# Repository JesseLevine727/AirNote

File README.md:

# AirNote

A touchless musical instrument built around a fully integrated RP2040,
VL53L1X distance sensor and MAX98357A speaker amplifier. One hand selects
eleven pentatonic notes over two octaves. The design uses a four-layer PCB
and factory assembly, with an external 8 ohm speaker.

**Engineering prototype, rev 0.2. The first-article order package has passed
static review and is ready to order; nothing is ordered or physically validated yet.**
Use [the independent review status](reviews/REVIEW_STATUS.md) for current
failures, passes and pending evidence. A schematic check or firmware build
does not establish that the assembled instrument works.

## Open the design

Open [hardware/airnote.kicad_pro](hardware/airnote.kicad_pro) in KiCad 9.0.9
or newer. The project contains three schematic sheets and the PCB. Project
libraries accompany the files. The generated schematic can also be read in
[hardware/outputs/airnote-schematic.pdf](hardware/outputs/airnote-schematic.pdf).

[View the PCB render](hardware/outputs/airnote-board.png). Some parts, including
the volume pot, mute switch and amplifier, have no installed 3D body model;
the render shows their footprints. Use the BOM and assembly drawing for the
fitted-part list, and verify mechanical dimensions from their drawings.

The [BOM](hardware/bom.csv) identifies exact components with their LCSC part
numbers for JLCPCB assembly. The fabricator, stackup and USB geometry are
recorded in the [fabrication plan](docs/fabrication_plan.md); stock and
prices are a snapshot and must be re-checked on the day of ordering.
Manufacturing outputs remain engineering review artifacts until the
independent review of the current revision passes.

## Try the sound

[Listen to the synthesized scale](artifacts/synth-preview.wav). This WAV is
rendered by the same software oscillator used in firmware; it is **not a
recording of the PCB, amplifier or speaker**.

## Build and verify

Run from this directory. Native behavioral tests need CMake and a C++17
compiler; the device build additionally needs `arm-none-eabi-gcc`, Python 3
and Git. KiCad's Python module is used by the hardware tools.

```sh
cmake -S . -B build/host
cmake --build build/host -j 4
ctest --test-dir build/host --output-on-failure

python3 tools/fetch_dependencies.py
cmake -S firmware -B build/firmware
cmake --build build/firmware -j 8
```

The firmware build produces `build/firmware/airnote.uf2` and `airnote.elf`.
The captured build is also available as [artifacts/airnote.uf2](artifacts/airnote.uf2),
with source and binary checksums in `artifacts/firmware-evidence.json`.
The SDK may fetch/build its own `picotool` utility on the first build. Runtime
dependencies are pinned in `tools/fetch_dependencies.py`; the vendored sensor
and audio transport adaptations retain their licenses and provenance.

To regenerate the software sound preview:

```sh
build/host/render_demo artifacts/synth-preview.wav
```

Independent reviewer tests and artifact checks live in `reviews/`. The
reviewer owns those checks separately from the implementation. Their result
reports distinguish logic/net-mapping evidence from routing and physical tests.

## Documents

- [Requirements, targets and three-agent workflow](docs/requirements.md)
- [Bring-up, programming, equipment and calibration procedure](docs/bringup.md)
- [Power and thermal allocations](docs/power_budget.md)
- [Fabrication and sourcing plan (JLCPCB)](docs/fabrication_plan.md)
- [Draft factory assembly brief](docs/assembly_request.md)
- [Independent review checklist](reviews/CHECKLIST.md)
- [Current review status](reviews/REVIEW_STATUS.md)
- [Exact part list](hardware/bom.csv)
- [Firmware pin assignment](firmware/include/boards/airnote.h)

Normal PLAY operation uses a specified 5 V adapter; programming/USB diagnostics
use the hardware MUTE position. Firmware also latches a USB host mute, starts
peripherals only after configuration or a deliberate adapter PLAY sequence,
and parks audio after USB suspend/deconfiguration until power-cycle. These
policies do not replace current/inrush/suspend measurements. The initial
distance correction is zero and has not been calibrated to a physical board.

The overseer coordinates the specification and integration, the implementer
creates the hardware, and the reviewer independently checks the artifacts and
tests. Neither factory assembly nor clean ERC/DRC counts as physical validation.

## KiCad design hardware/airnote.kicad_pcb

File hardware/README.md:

# AirNote hardware — engineering prototype

Open **airnote.kicad_pro** in KiCad 9. The three editable schematic sheets and routed four-layer PCB are the canonical design. The current native checks report **0 ERC violations; 0 DRC violations, 0 unconnected items and 0 schematic/PCB parity issues**. These are software checks; a physical board has not been built or tested.

- [Schematic PDF](outputs/airnote-schematic.pdf)
- [Board render](outputs/airnote-board.png)
- [Assembly drawing, including component references](outputs/airnote-assembly.pdf)
- [Four copper layers](outputs/airnote-copper.pdf)
- [Exact component BOM](bom.csv)
- [Draft fabrication and assembly exports](outputs/DRAFT-fabrication/)
- [Native ERC](reports/erc-final.json) and [DRC](reports/drc-final.json)
- [Independent review](../reviews/REVIEW_STATUS.md)

The render is illustrative: some exact component 3D models are absent, while their electrical footprints and assembly references remain present.

The board is 90 × 70 mm with four M2.5 mounting holes and three global fiducials (FID1 53.5/61.5, FID2 61.5/116.5, FID3 130.0/53.5 mm; 1 mm copper, 2 mm mask opening, board-only, excluded from BOM and position files). Signals route on F.Cu and B.Cu; In1.Cu and In2.Cu are ground reference planes. There are also outer ground pours. Minimum designed track/clearance is 0.15/0.127 mm; through vias are 0.45 mm copper with 0.20 mm drill. These are copper-path estimates from `reviews/inspect_trace_paths.py`, not measured supply integrity: IOVDD pin 22 to C6 about 2.9 mm (C6 GND pad via about 0.4 mm from the pad), DVDD pin 23 to C11 about 1.1 mm, IOVDD pin 33 to C7 about 1.6 mm and flash VCC to C15 about 3.1 mm. Crystal startup and oscillator margin remain bench checks.

The +5V rail after F1 is 0.4 mm wide (rev 0.2 review follow-up). F1 → U3 input and C16 is now 36.6 mm of 0.4 mm F.Cu with no vias, about 0.05 Ω estimated; it was 0.15 mm and about 0.12 Ω. F1 → U5 VDD/PVDD is 0.4 mm on F.Cu and on the B.Cu run, about 0.12 Ω estimated; it was 0.15 mm and about 0.31 Ω. At U5 the B.Cu-to-F.Cu change now has two vias in parallel. The C21/C22 bulk link is 0.4 mm. Three short sections stay narrower:

- The U5 pin 7/8 stubs are 0.3 mm, the pad width.
- The U3 EN tie (pin 3 to pin 1) is 0.15 mm; it carries no load current.
- The single F.Cu-to-B.Cu via beside SW2 and C19 has no room for a second via without rerouting RUN and SENSOR_XSHUT.

Resistances are copper estimates, not measurements.

The MCU is RP2040 with W25Q16JVSNIQ flash and a 12 MHz crystal. VL53L1CXV0FY/1 uses 3.3 V AVDD, 3.3 V I2C pull-ups and explicit 2V8-mode initialization. MAX98357AETE+T drives an external 8 Ω speaker; neither speaker terminal may connect to ground. Its GAIN pin floats for 9 dB, and SD high selects LEFT; firmware sends the same sample in both channels. A 10 kΩ resistor between GP14 and AMP_SD limits contention when the hardware MUTE switch forces shutdown. A separate switch pole makes GP15 low in MUTE. The volume potentiometer has a 1 MΩ ADC pull-down so an open wiper tends toward silence.

| Function | RP2040 GPIO |
|---|---:|
| I2C SDA / SCL | 0 / 1 |
| VL53L1X XSHUT / interrupt | 2 / 3 |
| I2S data / bit clock / LR clock | 10 / 11 / 12 |
| Amplifier enable / active-low mute sense | 14 / 15 |
| Status LED / volume ADC | 25 / 26 |

Use a regulated USB 5 V supply rated at least 1 A for PLAY. Set MUTE before connecting a computer for programming. The 250 mA USB descriptor is a declaration, not a measurement. USB inrush, configured current, suspend current, regulator temperature and actual speaker power remain physical test gates. See [calculated power budget](../docs/power_budget.md) and [bring-up procedure](../docs/bringup.md).

Factory assembly is required for the optical LGA and MCU/amp exposed-pad packages. Before release, the assembler must confirm the exact MPN supply, four-layer stackup, optical-device dry/no-wash process, MSL handling, sensor liner removal, post-reflow offset calibration, paste stencil and exposed-pad via fill/cap or equivalent validated process. The board includes thermal vias in the MCU and amplifier exposed pads. The external speaker, mating cable and power adapter are not PCBA BOM items. Through-hole controls/connectors require an assembly quote as well. Verify actual switch lever direction against MUTE/PLAY silkscreen during bring-up. No parts or boards have been ordered and no quoted total cost is available.

## Layout and sourcing notes

### Stackup

The board stackup is JLCPCB JLC04161H-7628, the chosen stackup per `docs/fabrication_plan.md` (1.6 mm nominal; KiCad sum 1.606 mm including 0.01 mm masks): F.Cu 0.035 / 7628 prepreg 0.2104 mm, εr 4.4 / In1.Cu 0.0152 / core 1.065 mm, εr 4.6 / In2.Cu 0.0152 / 7628 prepreg 0.2104 mm, εr 4.4 / B.Cu 0.035, solder mask both sides (εr 3.8). Re-check the stackup code on the order form. The copper finish is deliberately left unset in CAD (`None` in the Gerber job) because it is chosen on the order form: ENIG recommended, lead-free HASL acceptable. That is the user's decision.

### USB geometry

USB_DP, USB_DM, USB_DP_ESD, USB_DM_ESD, USB_DP_MCU and USB_DM_MCU are net class `USB_DIFF`: 0.25 mm traces, 0.15 mm pair gap (about 90 Ω differential on this stackup by the overseer's 2D field-solver estimate; USB full speed tolerates 90 Ω ±15%), 0.2 mm clearance to other nets, and a custom rule that keeps the outer GND pour 0.5 mm away so the pair is edge-coupled microstrip rather than coplanar. Neck-down to 0.15 mm happens at the J1, D1 and U1 pads, including two runs of about 3 mm through D1's pad gap. About 85% of each polarity runs at exactly 0.40 mm pitch. The uncoupled remainder is the J1 fan-out and duplicate-contact joins, the D1 pad entries and the staggered R8/R9. The whole path is on F.Cu with **zero vias**, over continuous In1.Cu GND (a script samples the trace footprint plus 0.1 mm and finds no In1 void or antipad under it).

- J1: the duplicated contacts are joined by short 0.15 mm stubs: DP (A6–B6) behind the pad row under the receptacle body, DM (A7–B7) in front of it. The pair leaves from B6/A7.
- D1 (USBLC6-2SC6) is about 15 mm along the pair from J1. The schematic order J1 → D1 → R8/R9 → U1 needs the pair to swap sides twice; both swaps happen inside D1 without vias. USB_DM runs through the gap between D1's pad columns to pin 3, and USB_DP_ESD leaves pin 6 through the same gap, using D1's internal pin 1–6 and 3–4 links as the crossovers. VBUS_RAW (pin 5) and GND (pin 2, own via) leave from the outer pad ends.
- R8/R9 sit side by side about 3 mm above U1 pins 47/46. The R → U1 section is matched within 0.23 mm (3.30 / 3.53 mm).
- Lengths, pad edge to pad edge, along the B6 and A7 trunks (reviewer's measurement, `reviews/layout-review.json`): J1 → D1 13.80 mm DP / 15.61 mm DM; D1 → R8/R9 43.66 / 41.40 mm; R8/R9 → U1 3.30 / 3.53 mm.
  - The per-section difference of about ±2 mm in the first two sections comes from where the D1 crossover puts the gap run (before the package for DM, after it for DP).
  - Through D1, the J1 → U1 totals are 60.76 mm DP and 60.53 mm DM, a 0.23 mm skew.
  - The USB-C duplicate-contact joins add orientation-dependent skew: up to about 2.8 mm with the plug on A6/A7 and 0.8 mm on B6/B7. That is about 17 ps, negligible against the 83 ns full-speed bit time.
- The pair is about 60 mm long (previously about 50 mm, routed as separate nets). It goes around the east side of the flash and approaches U1 from the north.
- USB impedance and differential behaviour are **not measured**. These are layout checks only. Request impedance control or an impedance coupon from the fabricator if the actual differential impedance matters.

### Crystal and RP2040 supply pins

Y1 (rotated −90°) sits directly below U1 pins 20/21. XIN is about 4.0–4.1 mm from pin 20 to Y1 pin 1 on F.Cu with no vias. XOUT runs about 0.8 mm straight into R1 (1 kΩ). XTAL_OUT runs about 4.1 mm from R1 pin 2, down the gap between Y1's pad columns, to Y1 pin 3. C1 and C2 are about 1 mm from Y1 pins 1 and 3 and have their own GND vias. Y1 GND pads 2 and 4 each have a GND via. U1 pin 19 GND, C5 and the F.Cu GND pour surround the network. No unrelated signal runs on F.Cu between the crystal network and U1 or under the crystal. The JLC listing for this crystal gives CL = 10 pF. C1/C2 stay at 15 pF: with about 3 pF stray that is about 10.5 pF, the RP2040 hardware design guide values. Frequency offset and startup margin must be measured at bring-up.

### Sourcing

`bom.csv` and every fitted schematic symbol carry an `LCSC` part number, and fitted footprints carry hidden `MPN`/`LCSC` fields for BOM/CPL generation. Passives use JLC Basic parts. R8/R9 (27 Ω, C25190) are JLC Extended. **Correction:** U2 is now W25Q16JVSNIQ, the 150-mil SOIC-8 that matches the placed SOIC-8_3.9x4.9 footprint. The previous W25Q16JVSSIQ is the 208-mil package, a part/footprint mismatch. Other substitutions:

- J1 is USB4105-GF-A-120 (same land pattern, 1.20 mm shell stakes).
- J2 is a generic straight 1x5 2.54 mm header (C32713271).
- RV1 is PTV09A-4015F-B103 (bushingless, 15 mm flat shaft). Bourns gives one recommended layout for all rear-mount PTV09 configurations, so the existing footprint is unchanged. The knob sits about 5 mm lower than with -1020F.

### Rev 0.2 review fixes

- The J1 shell stitching via at (67.80, 56.12) is removed (MFG-05). Its drill was 0.13 mm from the S1 shell slot, and the S1 pads are solid in GND on every layer.
- The reviewer's drill-web check (`reviews/inspect_layout.py`) now passes: via to via ≥ 0.2 mm, via to pad hole ≥ 0.45 mm.
- The C15 GND-pad via moved to (95.34, 66.94); its drill edge is 0.15 mm outside the pad.
- The board is marked rev 0.2: silkscreen "v0.2 ENGINEERING PROTOTYPE", PCB title block AirNote / 0.2 / 2026-10-10 (the Gerber job revision reads 0.2), and schematic title blocks rev 0.2.
- B.Silkscreen carries `JLCJLCJLCJLC` at (70, 90) so JLC prints its order number there.
- The JLC order files are generated by `tools/export_outputs.py`. See [the export README](outputs/DRAFT-fabrication/README.md) for upload steps.

## Re-export and regeneration

With KiCad 9 CLI installed, run from the repository root:

```sh
/usr/bin/python3 hardware/tools/export_outputs.py
```

This runs ERC and DRC, refuses failed checks, and regenerates PDF, render, Gerbers, drills, fitted BOM/positions, the JLC order files and an SHA-256 artifact manifest. It does not edit the canonical schematic or PCB. Position coordinates use KiCad's absolute origin in millimeters, with exported Y convention; the assembler must confirm rotations/origin. Test pads, mounting holes and fiducials are excluded from the position files. The export also writes the JLCPCB order package: `airnote-jlc-bom.csv`, `airnote-jlc-cpl.csv` (KiCad rotations, uncorrected) and `airnote-jlc-gerbers.zip`, all hashed in the artifact manifest.

`generate_hardware.py` creates only an initial schematic/placement in a **fresh separate directory**:

```sh
/usr/bin/python3 hardware/tools/generate_hardware.py --output-dir /tmp/airnote-rebuild
```

It intentionally refuses the canonical `hardware/` directory or an existing PCB output. The generator does **not** reproduce the final routed board: subsequent placement and local routing corrections live in the canonical editable PCB. Its output is a design-development starting point, not a replacement manufacturing source. Other scripts in `tools/` record the development routing stages and can overwrite a working PCB; do not rerun those on the canonical design. Historical router sessions and intermediate `reports/*.kicad_pcb` boards are development evidence, not order candidates. Use only `*-final.json` reports and the current artifact hashes for the final checkpoint. The custom rules in `airnote.kicad_dru` now carry explicit units; the earlier unit-less file was rejected by KiCad, so those rules had not been applied before.

Project-local libraries include a datasheet-correct MAX98357A exposed-pad symbol and exact ADI 90-0031 land pattern. J1's local footprint differs from the installed KiCad footprint only in two unplated peg-hole layer masks: `F&B.Cu` becomes `*.Cu`, matching KiCad's four-layer normalization. Pad locations, dimensions, drills, shell slots and contact mapping are unchanged. Standard native library footprints are embedded in the PCB and additional snapshots are retained locally.

References: [RP2040 hardware design guide](https://datasheets.raspberrypi.com/rp2040/hardware-design-with-rp2040.pdf), [official reference source](https://datasheets.raspberrypi.com/rp2040/Minimal-KiCAD.zip), [ST VL53L1X datasheet](https://www.st.com/resource/en/datasheet/vl53l1x.pdf), [MAX98357A datasheet](https://www.analog.com/media/en/technical-documentation/data-sheets/MAX98357A-MAX98357B.pdf), [ADI land pattern 90-0031](https://mds.analog.com/api/public/content/90-0031.pdf), [Bourns potentiometer drawing](https://www.bourns.com/docs/product-datasheets/ptv09.pdf). The downloaded Raspberry Pi source retains its original license in `reference/`; KiCad library snapshots originate from the installed KiCad libraries and retain their upstream licensing.

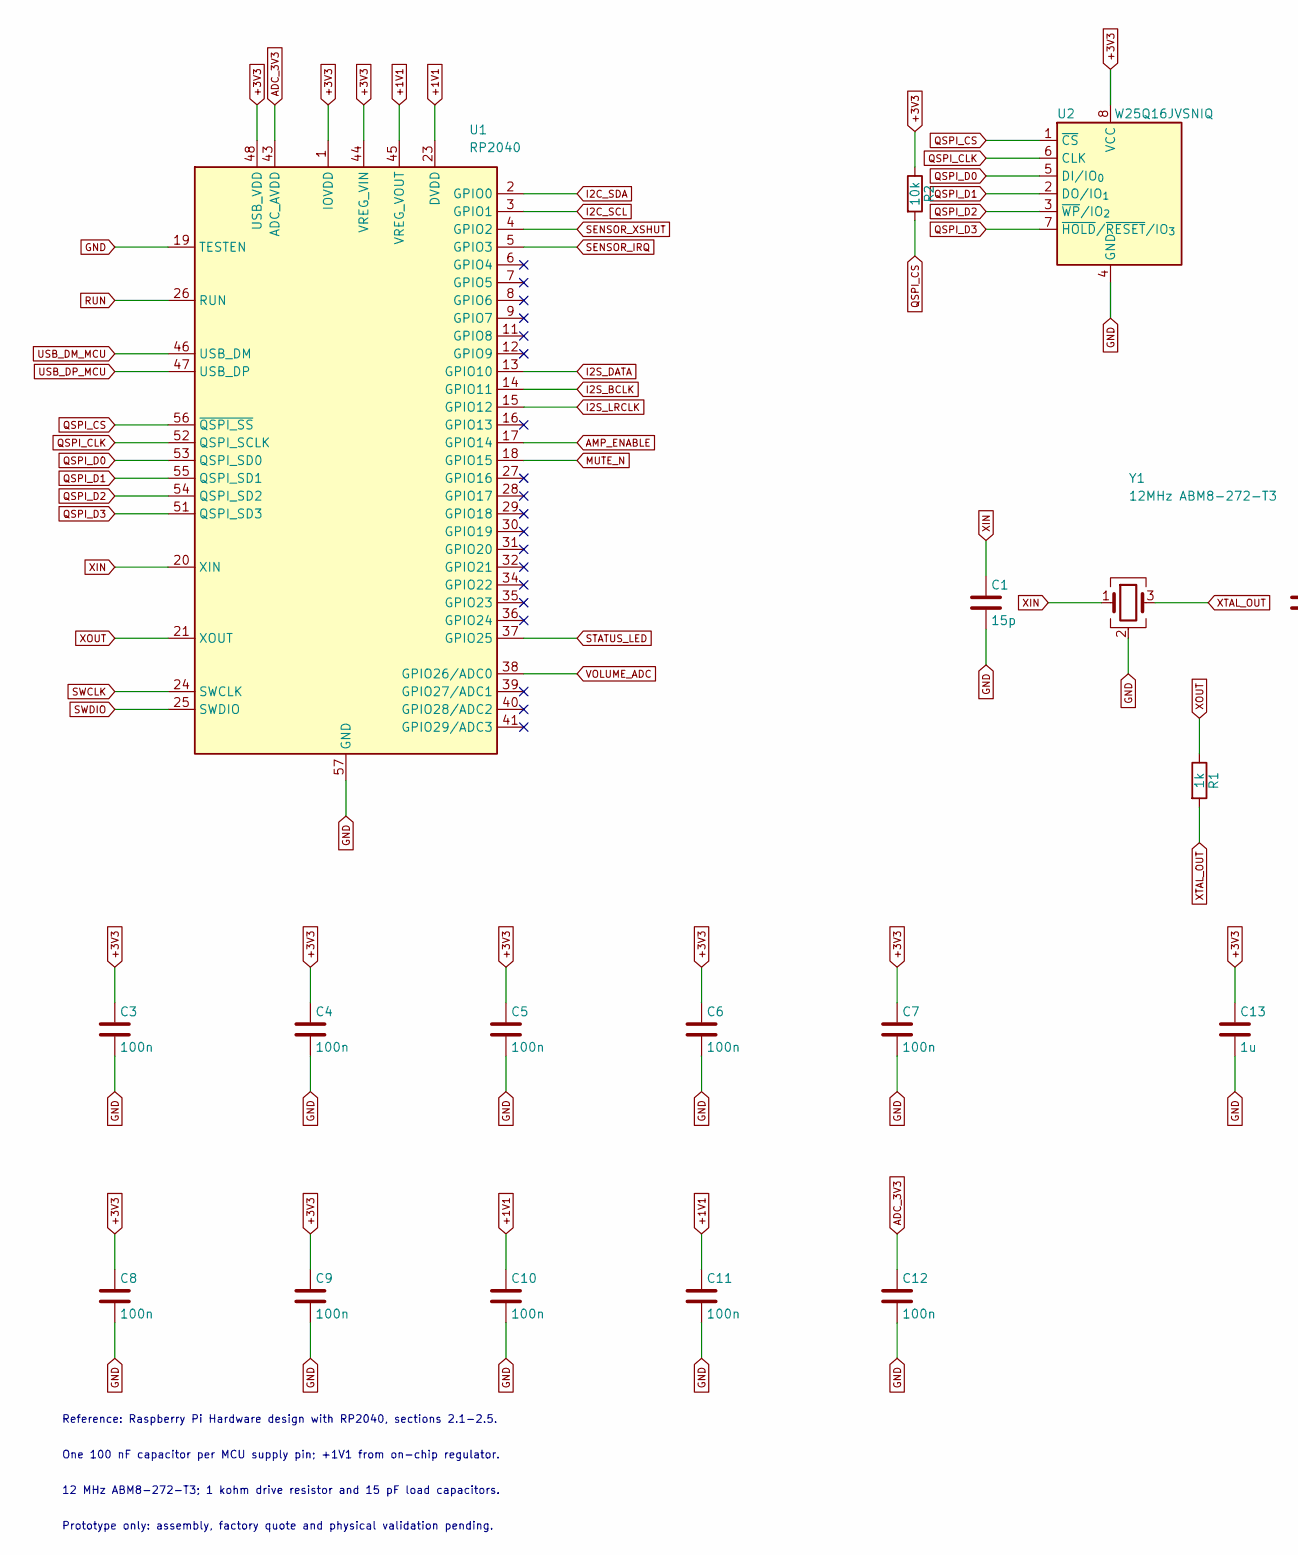
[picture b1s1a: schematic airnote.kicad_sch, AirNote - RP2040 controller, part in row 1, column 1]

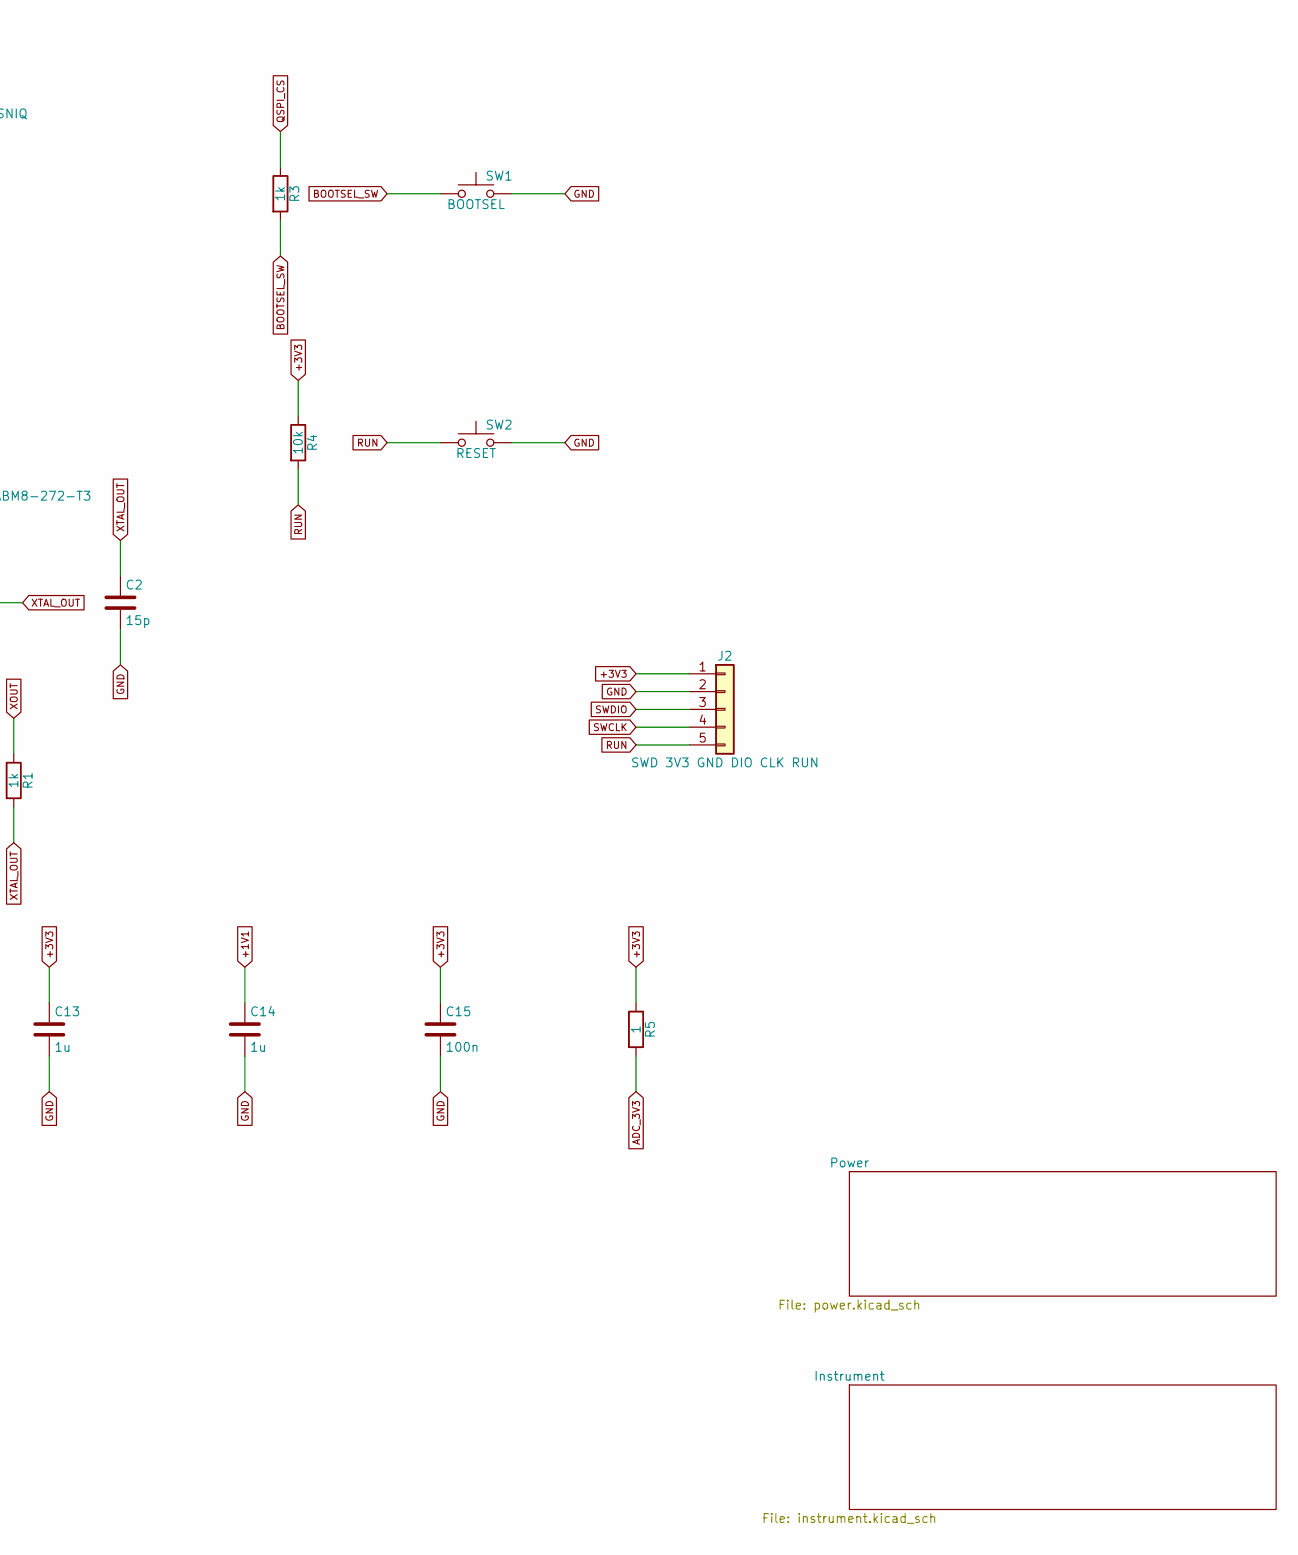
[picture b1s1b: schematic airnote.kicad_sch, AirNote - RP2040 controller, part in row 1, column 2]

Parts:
C1, C2: 15p; C_0603_1608Metric; MPN CL10C150JB8NNNC; LCSC C1644
C3, C4, C5, C6, C7, C8, C9, C10, C11, C12, C15: 100n; C_0603_1608Metric; MPN CC0603KRX7R9BB104; LCSC C14663
C13, C14: 1u; C_0603_1608Metric; MPN CL10A105KB8NNNC; LCSC C15849
J2: SWD 3V3 GND DIO CLK RUN; PinHeader_1x05_P2.54mm_Vertical; MPN HX PZ2.54-1x5P ZZ; LCSC C32713271
R1, R3: 1k; R_0603_1608Metric; MPN 0603WAF1001T5E; LCSC C21190
R2, R4: 10k; R_0603_1608Metric; MPN 0603WAF1002T5E; LCSC C25804
R5: 1; R_0603_1608Metric; MPN 0603WAF100KT5E; LCSC C22936
SW1: BOOTSEL; SW_SPST_TL3342; MPN TL3342F160QG; LCSC C2886898
SW2: RESET; SW_SPST_TL3342; MPN TL3342F160QG; LCSC C2886898
U1: RP2040; QFN-56-1EP_7x7mm_P0.4mm_EP3.2x3.2mm; MPN RP2040; LCSC C2040
U2: W25Q16JVSNIQ; SOIC-8_3.9x4.9mm_P1.27mm; MPN W25Q16JVSNIQ; LCSC C2456211
Y1: 12MHz ABM8-272-T3; Crystal_SMD_3225-4Pin_3.2x2.5mm; MPN ABM8-272-T3; LCSC C20625731

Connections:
+1V1: C10.1, C11.1, C14.1, U1.23 (DVDD), U1.45 (VREG_VOUT), U1.50 (DVDD); also elsewhere on the board
+3V3: C3.1, C4.1, C5.1, C6.1, C7.1, C8.1, C9.1, C13.1, C15.1, J2.1, R2.1, R4.1, R5.1, U1.1 (IOVDD), U1.10 (IOVDD), U1.22 (IOVDD), U1.33 (IOVDD), U1.42 (IOVDD), U1.44 (VREG_VIN), U1.48 (USB_VDD), U1.49 (IOVDD), U2.8 (VCC); also elsewhere on the board
ADC_3V3: C12.1, R5.2, U1.43 (ADC_AVDD)
AMP_ENABLE: U1.17 (GPIO14); also elsewhere on the board
BOOTSEL_SW: R3.2, SW1.1
GND: C1.2, C2.2, C3.2, C4.2, C5.2, C6.2, C7.2, C8.2, C9.2, C10.2, C11.2, C12.2, C13.2, C14.2, C15.2, J2.2, SW1.2, SW2.2, U1.19 (TESTEN), U1.57 (GND), U2.4 (GND), Y1.2 (G), Y1.4 (G); also elsewhere on the board
I2C_SCL: U1.3 (GPIO1); also elsewhere on the board
I2C_SDA: U1.2 (GPIO0); also elsewhere on the board
I2S_BCLK: U1.14 (GPIO11); also elsewhere on the board
I2S_DATA: U1.13 (GPIO10); also elsewhere on the board
I2S_LRCLK: U1.15 (GPIO12); also elsewhere on the board
MUTE_N: U1.18 (GPIO15); also elsewhere on the board
QSPI_CLK: U1.52 (QSPI_SCLK), U2.6 (CLK)
QSPI_CS: R2.2, R3.1, U1.56 (~QSPI_SS), U2.1 (~CS)
QSPI_D0: U1.53 (QSPI_SD0), U2.5 (DI/IO_{0})
QSPI_D1: U1.55 (QSPI_SD1), U2.2 (DO/IO_{1})
QSPI_D2: U1.54 (QSPI_SD2), U2.3 (~WP/IO_{2})
QSPI_D3: U1.51 (QSPI_SD3), U2.7 (~HOLD/~RESET/IO_{3})
RUN: J2.5, R4.2, SW2.1, U1.26 (RUN)
SENSOR_IRQ: U1.5 (GPIO3); also elsewhere on the board
SENSOR_XSHUT: U1.4 (GPIO2); also elsewhere on the board
STATUS_LED: U1.37 (GPIO25); also elsewhere on the board
SWCLK: J2.4, U1.24 (SWCLK)
SWDIO: J2.3, U1.25 (SWDIO)
USB_DM_MCU: U1.46 (USB_DM); also elsewhere on the board
USB_DP_MCU: U1.47 (USB_DP); also elsewhere on the board
VOLUME_ADC: U1.38 (GPIO26/ADC0); also elsewhere on the board
XIN: C1.1, U1.20 (XIN), Y1.1
XOUT: R1.1, U1.21 (XOUT)
XTAL_OUT: C2.1, R1.2, Y1.3

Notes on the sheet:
Reference: Raspberry Pi Hardware design with RP2040, sections 2.1-2.5.
One 100 nF capacitor per MCU supply pin; +1V1 from on-chip regulator.
12 MHz ABM8-272-T3; 1 kohm drive resistor and 15 pF load capacitors.
Prototype only: assembly, factory quote and physical validation pending.

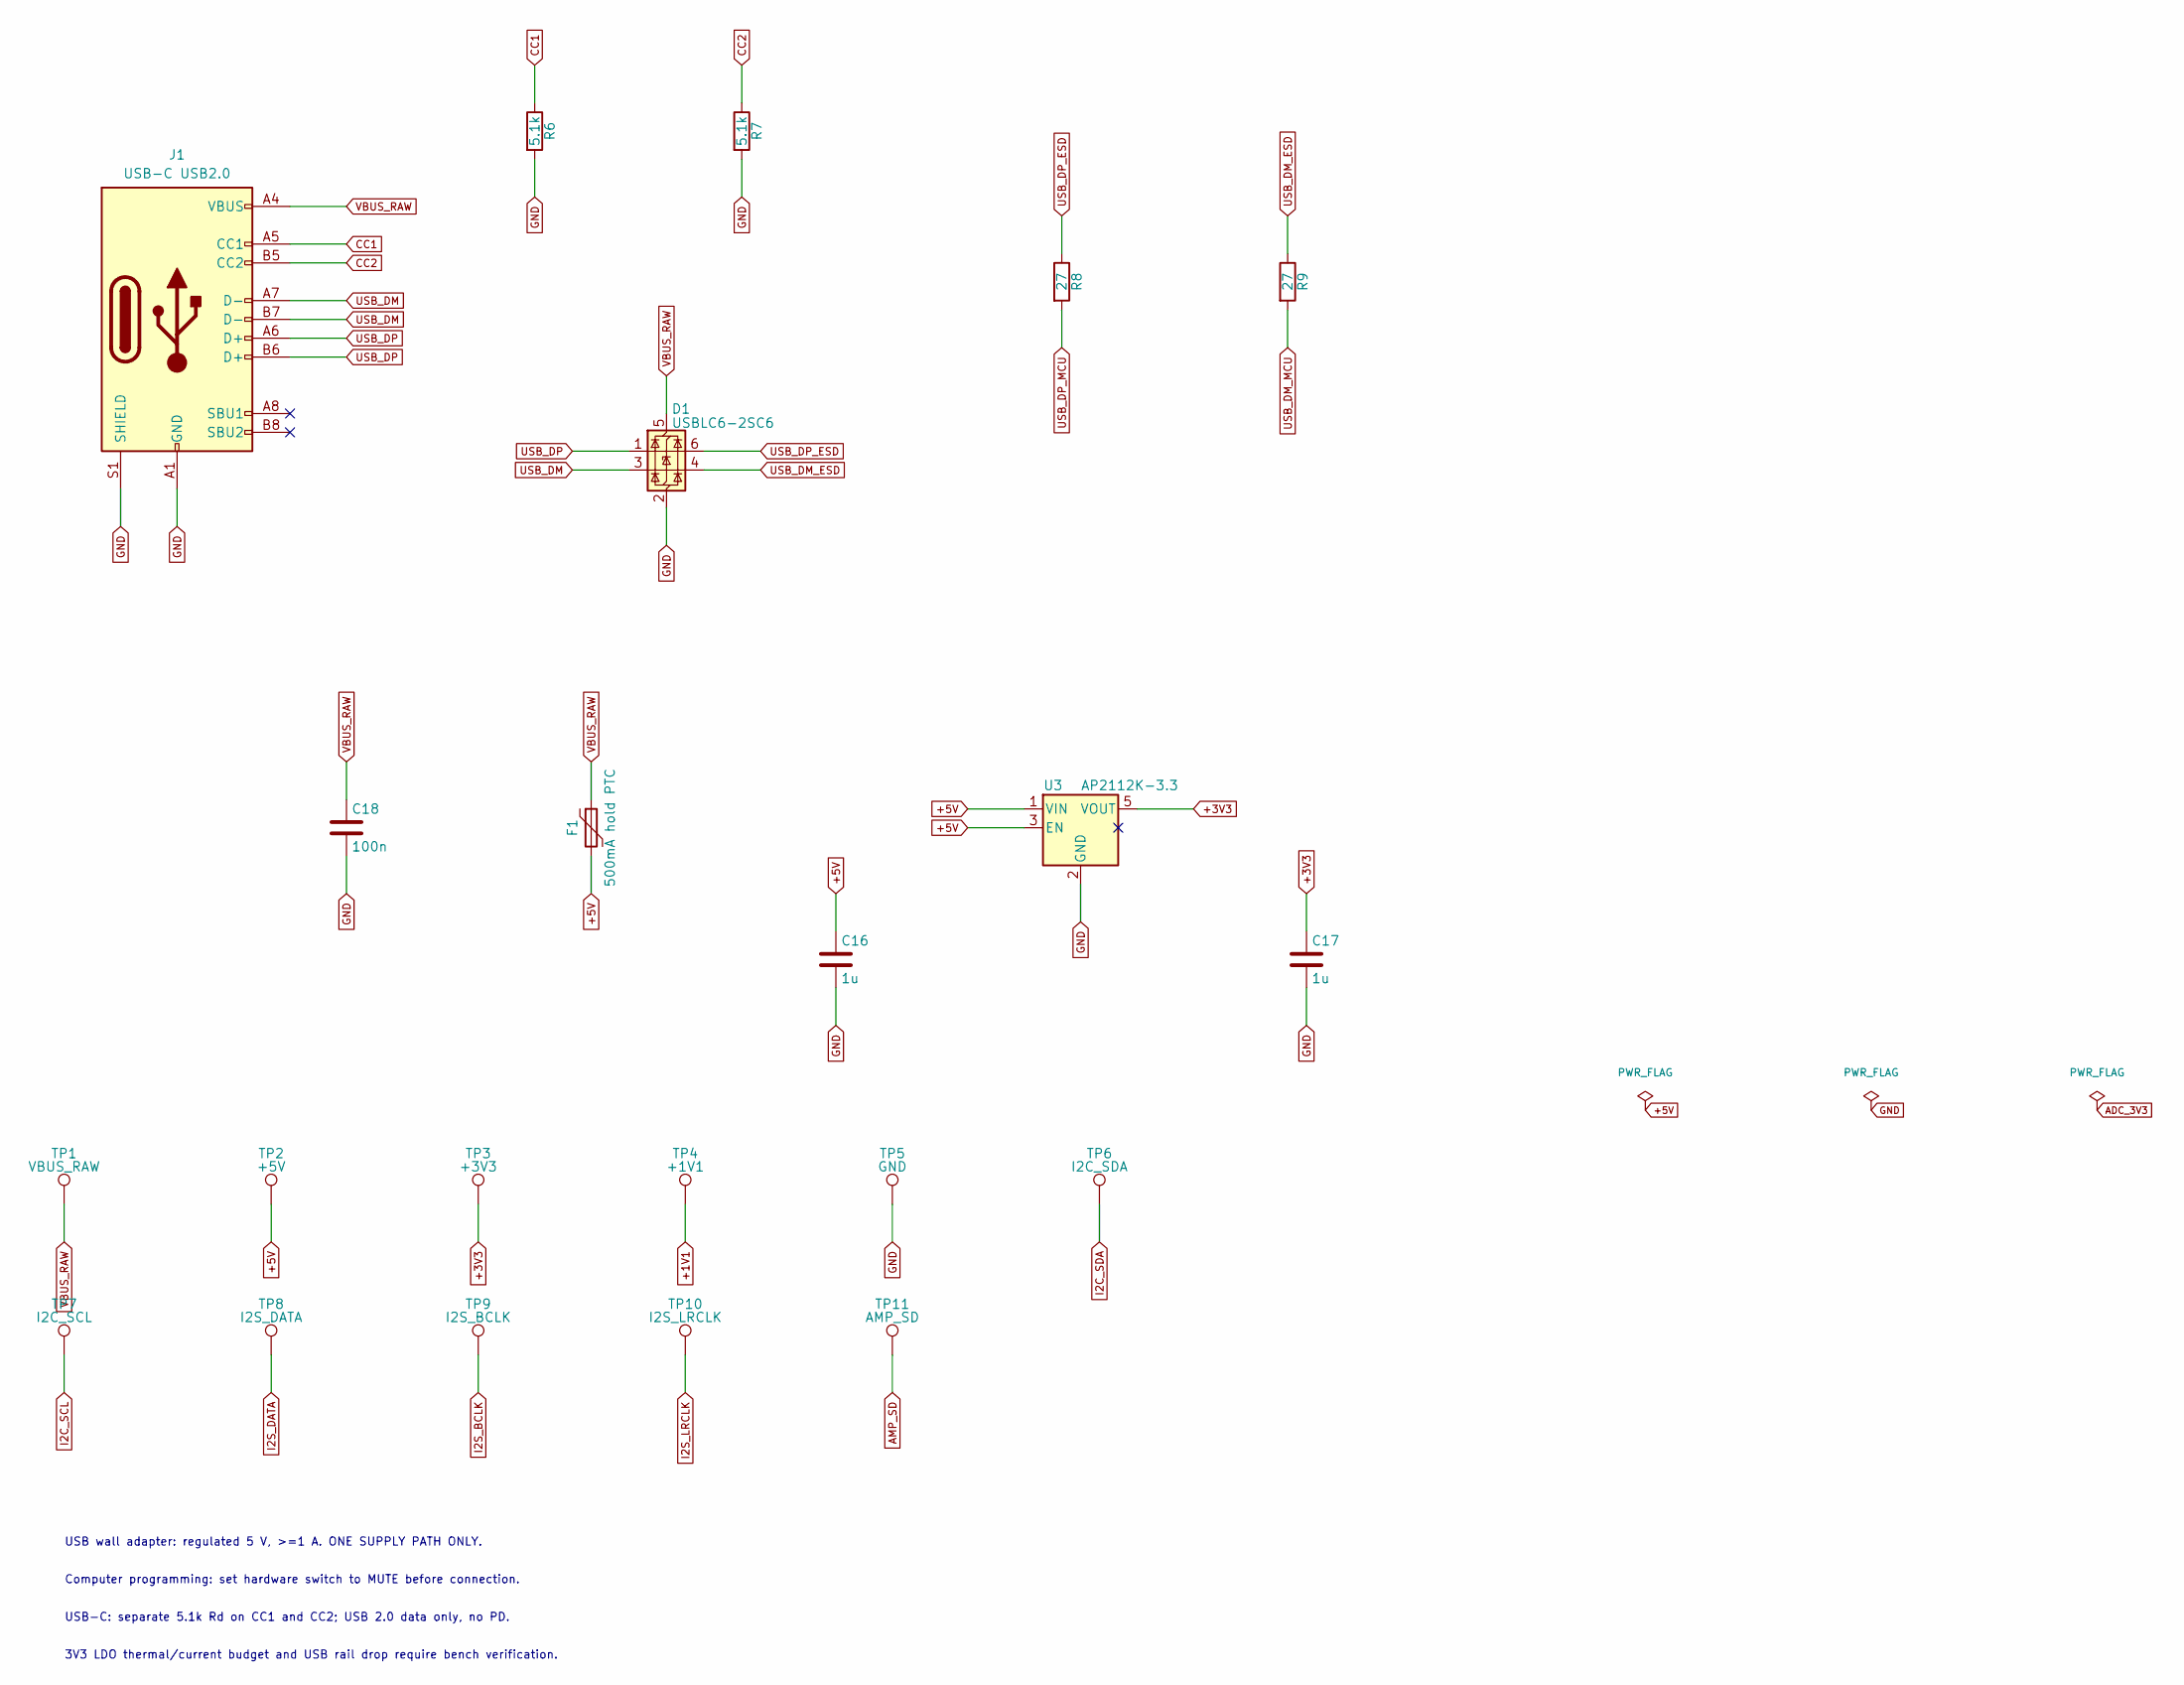
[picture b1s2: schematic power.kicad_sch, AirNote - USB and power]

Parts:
C16, C17: 1u; C_0603_1608Metric; MPN CL10A105KB8NNNC; LCSC C15849
C18: 100n; C_0603_1608Metric; MPN CC0603KRX7R9BB104; LCSC C14663
D1: USBLC6-2SC6; SOT-23-6; MPN USBLC6-2SC6; LCSC C7519
F1: 500mA hold PTC; Fuse_1206_3216Metric; MPN 1206L050YR; LCSC C163512
J1: USB-C USB2.0; USB_C_Receptacle_GCT_USB4105-xx-A_16P_TopMnt_Horizontal; MPN USB4105-GF-A-120; LCSC C5184243
R6, R7: 5.1k; R_0603_1608Metric; MPN 0603WAF5101T5E; LCSC C23186
R8, R9: 27; R_0603_1608Metric; MPN 0603WAF270JT5E; LCSC C25190
TP1: VBUS_RAW; TestPoint_Pad_D1.5mm; MPN TEST_PAD_1.5MM
TP2: +5V; TestPoint_Pad_D1.5mm; MPN TEST_PAD_1.5MM
TP3: +3V3; TestPoint_Pad_D1.5mm; MPN TEST_PAD_1.5MM
TP4: +1V1; TestPoint_Pad_D1.5mm; MPN TEST_PAD_1.5MM
TP5: GND; TestPoint_Pad_D1.5mm; MPN TEST_PAD_1.5MM
TP6: I2C_SDA; TestPoint_Pad_D1.5mm; MPN TEST_PAD_1.5MM
TP7: I2C_SCL; TestPoint_Pad_D1.5mm; MPN TEST_PAD_1.5MM
TP8: I2S_DATA; TestPoint_Pad_D1.5mm; MPN TEST_PAD_1.5MM
TP9: I2S_BCLK; TestPoint_Pad_D1.5mm; MPN TEST_PAD_1.5MM
TP10: I2S_LRCLK; TestPoint_Pad_D1.5mm; MPN TEST_PAD_1.5MM
TP11: AMP_SD; TestPoint_Pad_D1.5mm; MPN TEST_PAD_1.5MM
U3: AP2112K-3.3; SOT-23-5; MPN AP2112K-3.3TRG1; LCSC C51118

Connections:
+1V1: TP4.1; also elsewhere on the board
+3V3: C17.1, TP3.1, U3.5 (VOUT); also elsewhere on the board
+5V: C16.1, F1.2, TP2.1, U3.1 (VIN), U3.3 (EN); also elsewhere on the board
AMP_SD: TP11.1; also elsewhere on the board
CC1: J1.A5 (CC1), R6.1
CC2: J1.B5 (CC2), R7.1
GND: C16.2, C17.2, C18.2, D1.2 (GND), J1.A1 (GND), J1.A12 (GND), J1.B1 (GND), J1.B12 (GND), J1.S1 (SHIELD), R6.2, R7.2, TP5.1, U3.2 (GND); also elsewhere on the board
I2C_SCL: TP7.1; also elsewhere on the board
I2C_SDA: TP6.1; also elsewhere on the board
I2S_BCLK: TP9.1; also elsewhere on the board
I2S_DATA: TP8.1; also elsewhere on the board
I2S_LRCLK: TP10.1; also elsewhere on the board
USB_DM: D1.3 (I/O2), J1.A7 (D-), J1.B7 (D-)
USB_DM_ESD: D1.4 (I/O2), R9.1
USB_DM_MCU: R9.2; also elsewhere on the board
USB_DP: D1.1 (I/O1), J1.A6 (D+), J1.B6 (D+)
USB_DP_ESD: D1.6 (I/O1), R8.1
USB_DP_MCU: R8.2; also elsewhere on the board
VBUS_RAW: C18.1, D1.5 (VBUS), F1.1, J1.A4 (VBUS), J1.A9 (VBUS), J1.B4 (VBUS), J1.B9 (VBUS), TP1.1

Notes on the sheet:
USB wall adapter: regulated 5 V, >=1 A. ONE SUPPLY PATH ONLY.
Computer programming: set hardware switch to MUTE before connection.
USB-C: separate 5.1k Rd on CC1 and CC2; USB 2.0 data only, no PD.
3V3 LDO thermal/current budget and USB rail drop require bench verification.

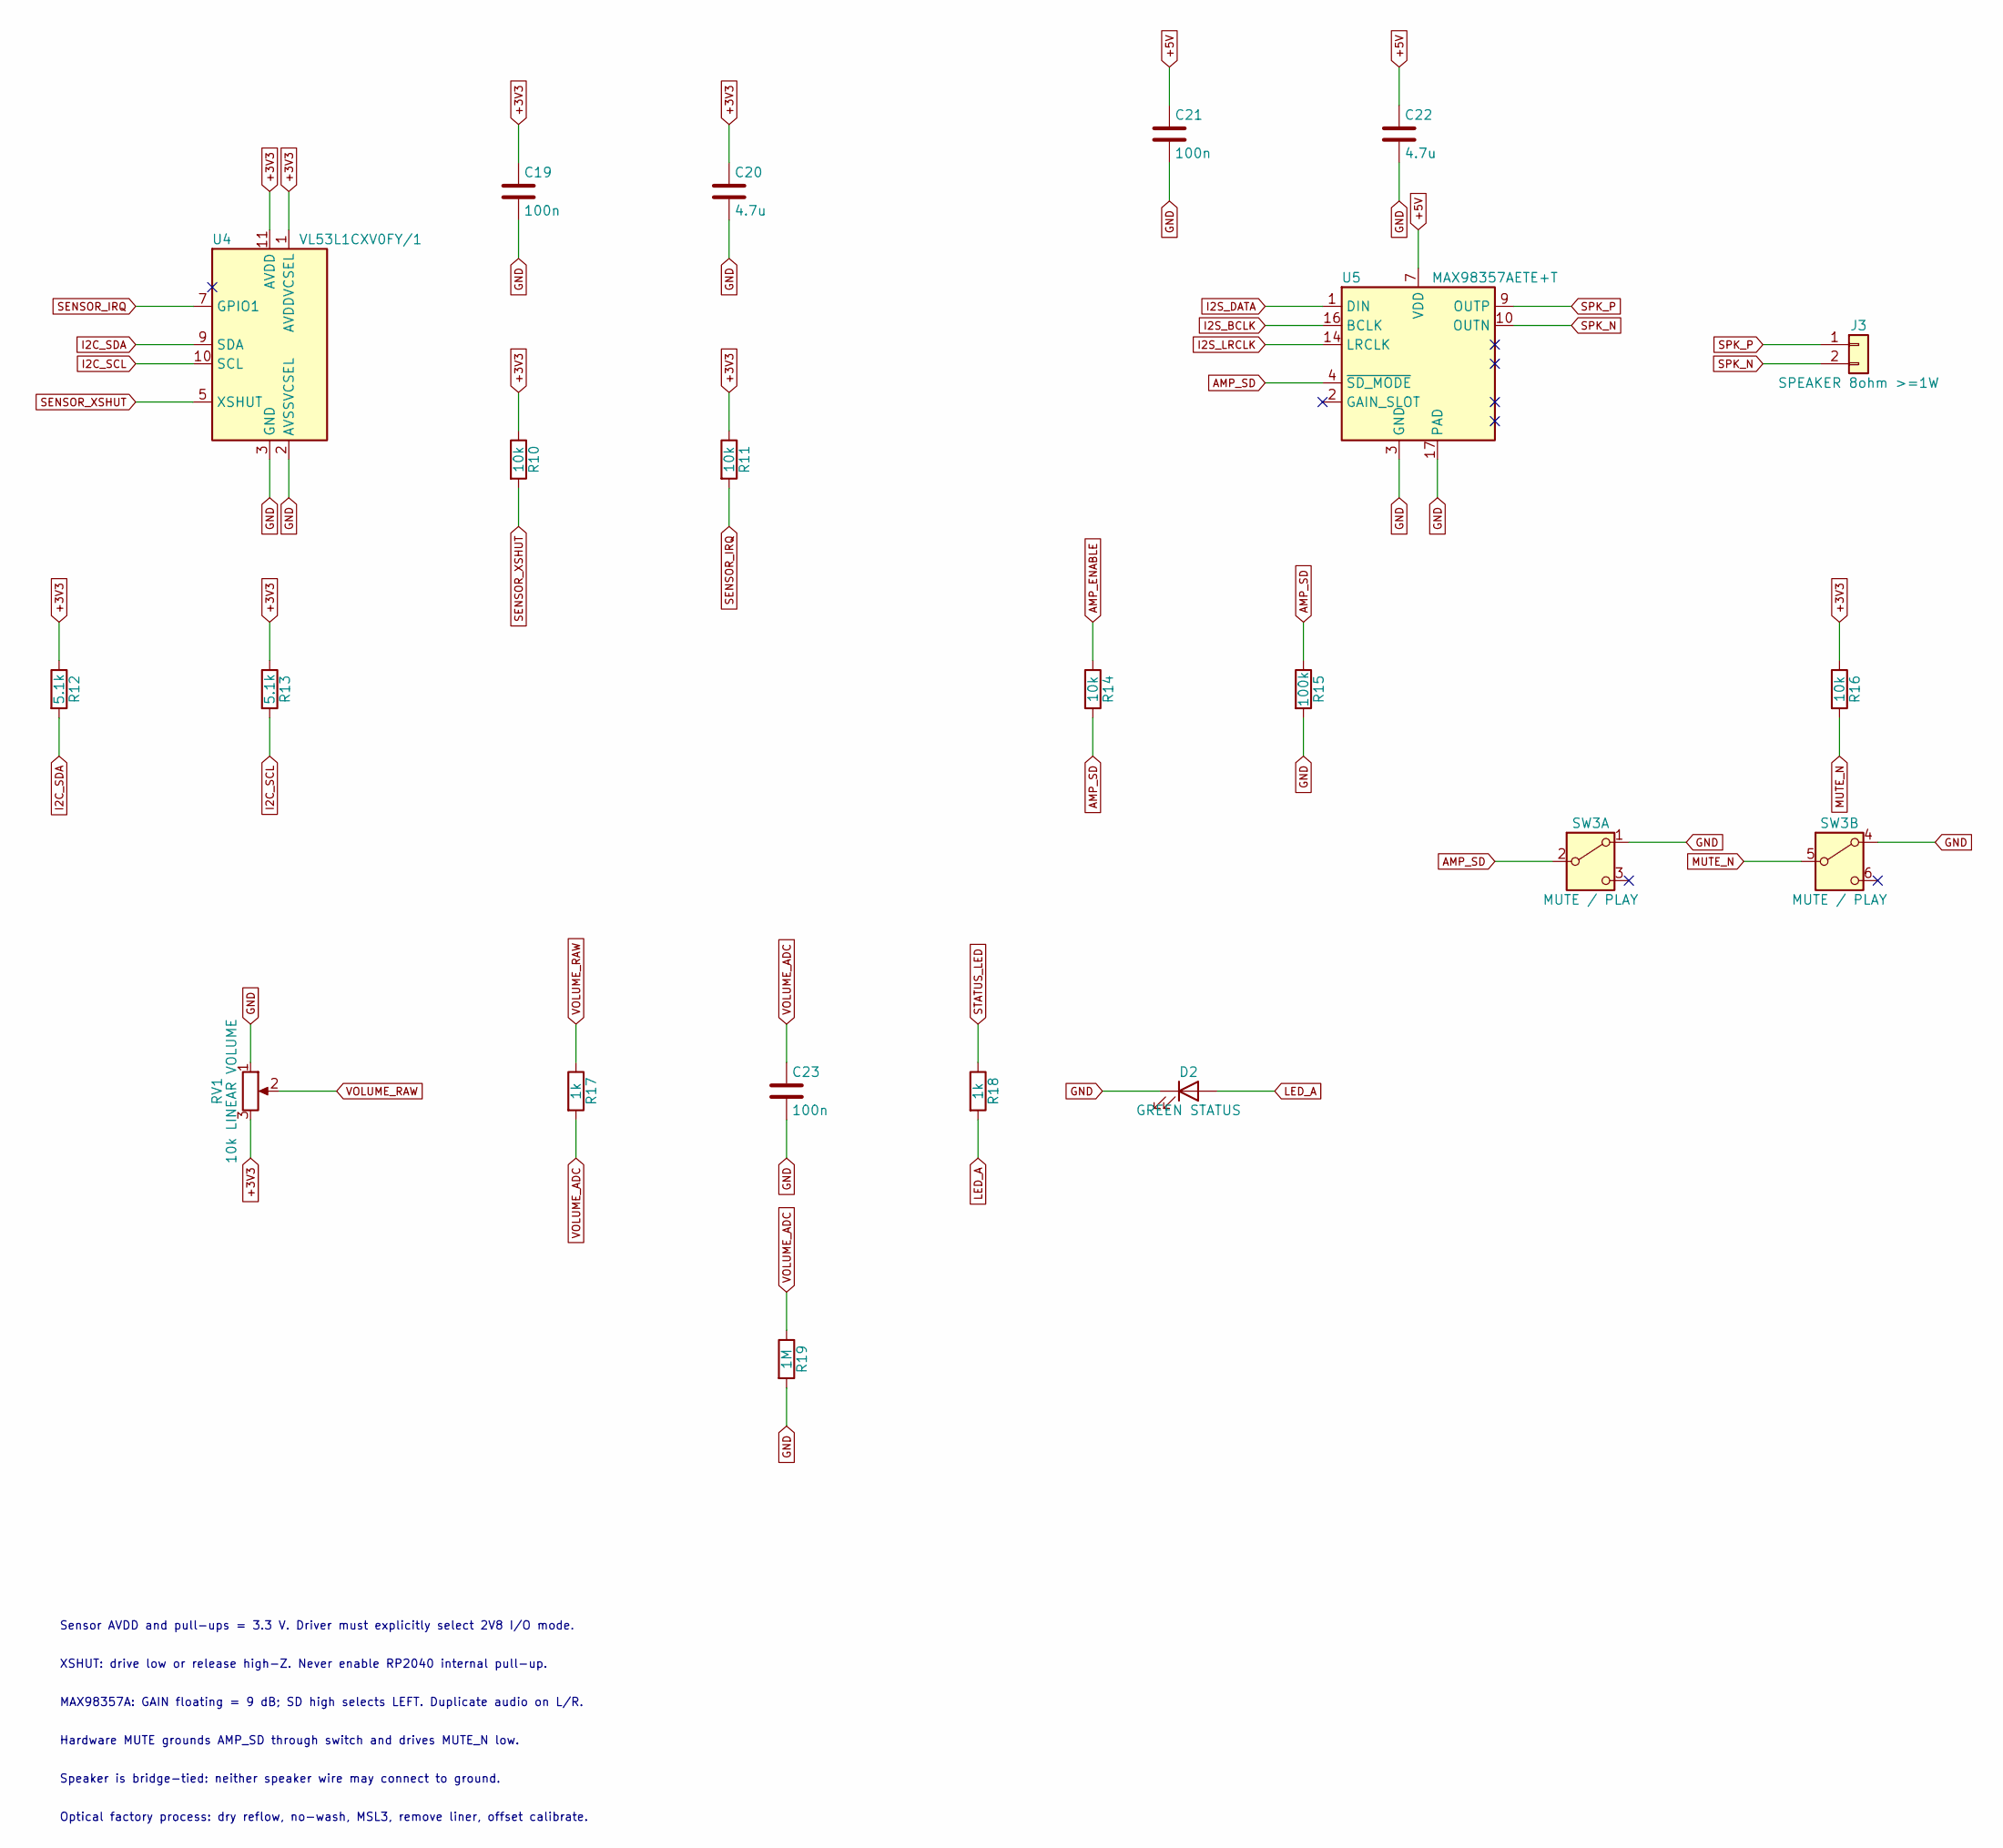
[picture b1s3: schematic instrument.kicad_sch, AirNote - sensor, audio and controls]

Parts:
C19, C21, C23: 100n; C_0603_1608Metric; MPN CC0603KRX7R9BB104; LCSC C14663
C20, C22: 4.7u; C_0805_2012Metric; MPN CL21A475KAQNNNE; LCSC C1779
D2: GREEN STATUS; LED_0603_1608Metric; MPN LTST-C190KGKT; LCSC C125094
J3: SPEAKER 8ohm >=1W; JST_PH_B2B-PH-K_1x02_P2.00mm_Vertical; MPN B2B-PH-K-S(LF)(SN); LCSC C131337
R10, R11, R14, R16: 10k; R_0603_1608Metric; MPN 0603WAF1002T5E; LCSC C25804
R12, R13: 5.1k; R_0603_1608Metric; MPN 0603WAF5101T5E; LCSC C23186
R15: 100k; R_0603_1608Metric; MPN 0603WAF1003T5E; LCSC C25803
R17, R18: 1k; R_0603_1608Metric; MPN 0603WAF1001T5E; LCSC C21190
R19: 1M; R_0603_1608Metric; MPN 0603WAF1004T5E; LCSC C22935
RV1: 10k LINEAR VOLUME; Potentiometer_Bourns_PTV09A-1_Single_Vertical; MPN PTV09A-4015F-B103; LCSC C5710902
SW3: MUTE / PLAY; SW_DPDT_CK_JS202011JCQN; MPN JS202011JCQN; LCSC C221665
U4: VL53L1CXV0FY/1; ST_VL53L1x; MPN VL53L1CXV0FY/1; LCSC C190004
U5: MAX98357AETE+T; MAX98357A_T1633_ADI_90-0031; MPN MAX98357AETE+T; LCSC C910544

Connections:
+3V3: C19.1, C20.1, R10.1, R11.1, R12.1, R13.1, R16.1, RV1.3, U4.1 (AVDDVCSEL), U4.11 (AVDD); also elsewhere on the board
+5V: C21.1, C22.1, U5.7 (VDD), U5.8 (VDD); also elsewhere on the board
AMP_ENABLE: R14.1; also elsewhere on the board
AMP_SD: R14.2, R15.1, SW3.2 (B), U5.4 (~SD_MODE); also elsewhere on the board
GND: C19.2, C20.2, C21.2, C22.2, C23.2, D2.1 (K), R15.2, R19.2, RV1.1, SW3.1 (A), SW3.4 (A), U4.2 (AVSSVCSEL), U4.3 (GND), U4.4 (GND), U4.6 (GND), U4.12 (GND), U5.3 (GND), U5.11 (GND), U5.15 (GND), U5.17 (PAD); also elsewhere on the board
I2C_SCL: R13.2, U4.10 (SCL); also elsewhere on the board
I2C_SDA: R12.2, U4.9 (SDA); also elsewhere on the board
I2S_BCLK: U5.16 (BCLK); also elsewhere on the board
I2S_DATA: U5.1 (DIN); also elsewhere on the board
I2S_LRCLK: U5.14 (LRCLK); also elsewhere on the board
LED_A: D2.2 (A), R18.2
MUTE_N: R16.2, SW3.5 (B); also elsewhere on the board
SENSOR_IRQ: R11.2, U4.7 (GPIO1); also elsewhere on the board
SENSOR_XSHUT: R10.2, U4.5 (XSHUT); also elsewhere on the board
SPK_N: J3.2, U5.10 (OUTN)
SPK_P: J3.1, U5.9 (OUTP)
STATUS_LED: R18.1; also elsewhere on the board
VOLUME_ADC: C23.1, R17.2, R19.1; also elsewhere on the board
VOLUME_RAW: R17.1, RV1.2

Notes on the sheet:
Sensor AVDD and pull-ups = 3.3 V. Driver must explicitly select 2V8 I/O mode.
XSHUT: drive low or release high-Z. Never enable RP2040 internal pull-up.
MAX98357A: GAIN floating = 9 dB; SD high selects LEFT. Duplicate audio on L/R.
Hardware MUTE grounds AMP_SD through switch and drives MUTE_N low.
Speaker is bridge-tied: neither speaker wire may connect to ground.
Optical factory process: dry reflow, no-wash, MSL3, remove liner, offset calibrate.
